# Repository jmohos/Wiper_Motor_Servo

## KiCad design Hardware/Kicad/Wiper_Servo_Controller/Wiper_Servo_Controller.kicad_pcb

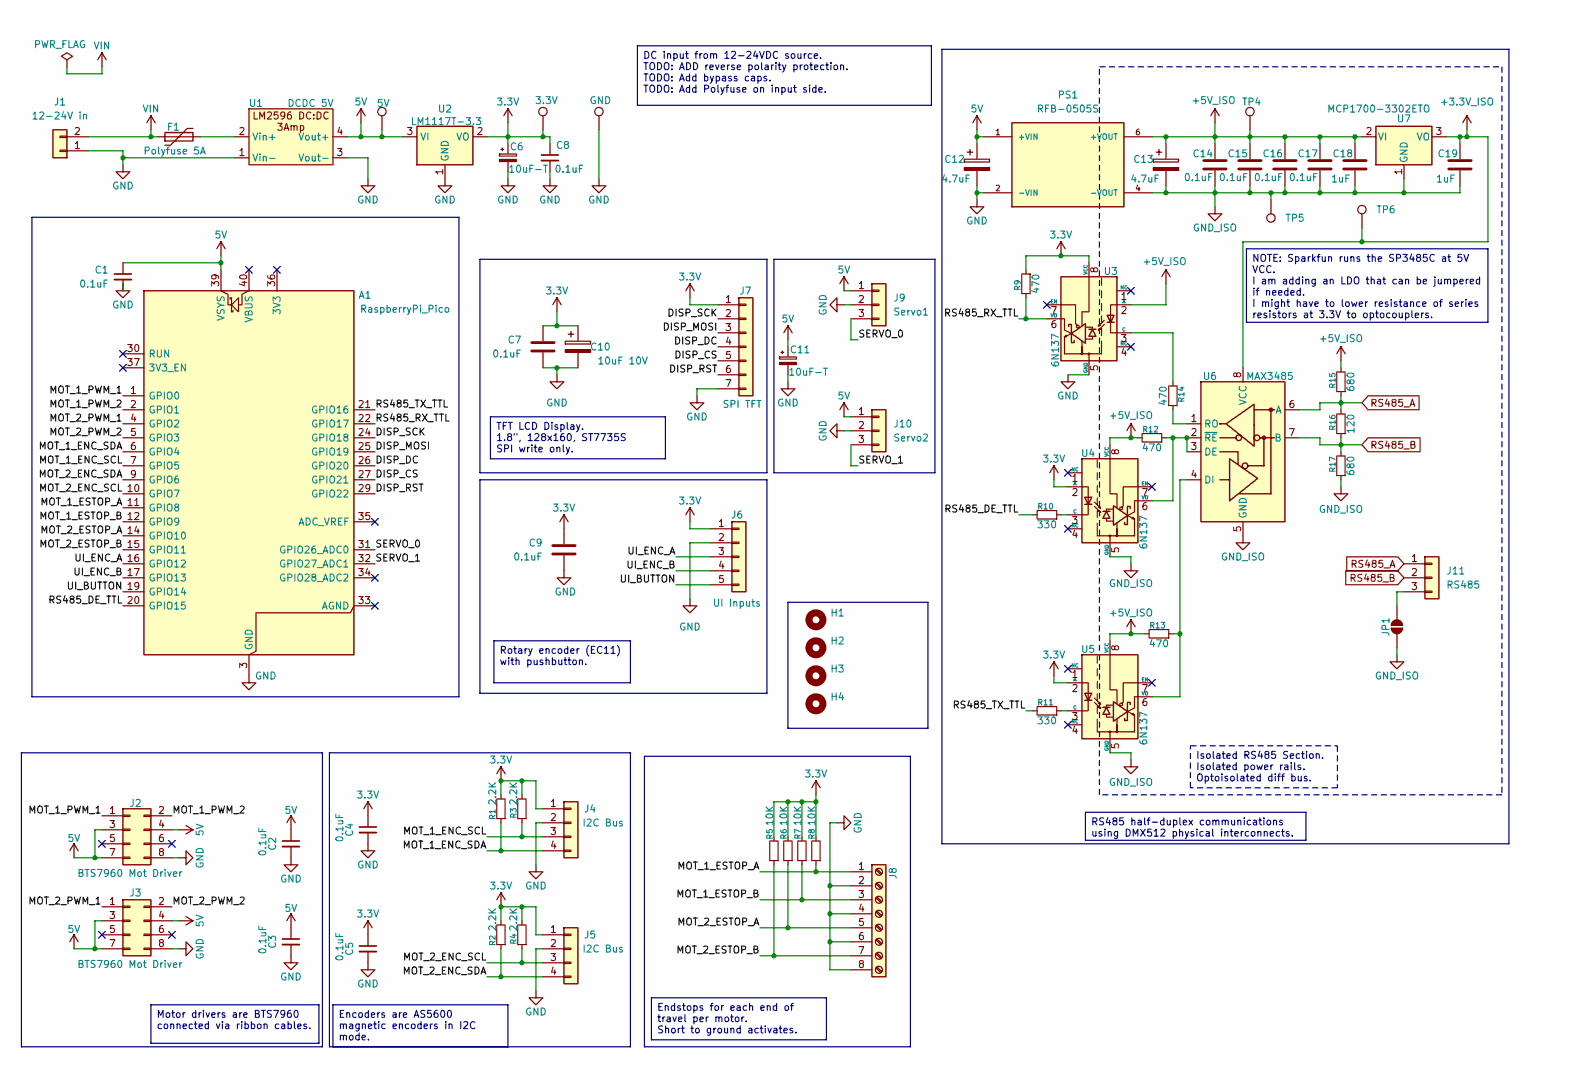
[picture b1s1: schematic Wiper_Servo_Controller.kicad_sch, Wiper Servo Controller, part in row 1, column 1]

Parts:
A1: RaspberryPi_Pico; RaspberryPi_Pico_Common_THT
C1, C2, C3, C4, C5, C7, C8, C9, C14, C15, C16, C17: 0.1uF; C_Disc_D5.1mm_W3.2mm_P5.00mm
C6, C11: 10uF-T; CP_Radial_Tantal_D5.5mm_P2.50mm
C10: 10uF 10V; CP_Radial_D5.0mm_P2.00mm
C12, C13: 4.7uF; CP_Radial_D5.0mm_P2.00mm
C18, C19: 1uF; C_Disc_D5.1mm_W3.2mm_P5.00mm
F1: Polyfuse 5A; Fuse_Littelfuse_395Series
H1, H2, H3, H4: MountingHole; MountingHole_3.2mm_M3
J1: 12-24V in; SolderWire-2sqmm_1x02_P7.8mm_D2mm_OD3.9mm
J2, J3: Conn_02x04_Odd_Even; IDC-Header_2x04_P2.54mm_Vertical
J4: Mot 1 Enc; JST_PH_B4B-PH-K_1x04_P2.00mm_Vertical
J5: Mot 2 Enc; JST_PH_B4B-PH-K_1x04_P2.00mm_Vertical
J6: UI Inputs; JST_PH_B5B-PH-K_1x05_P2.00mm_Vertical
J7: SPI TFT; JST_PH_B7B-PH-K_1x07_P2.00mm_Vertical
J8: Screw_Terminal_01x08; TerminalBlock_Phoenix_MPT-0,5-8-2.54_1x08_P2.54mm_Horizontal
J9: Servo1; JST_PH_B3B-PH-K_1x03_P2.00mm_Vertical
J10: Servo2; JST_PH_B3B-PH-K_1x03_P2.00mm_Vertical
J11: RS485; JST_PH_B3B-PH-K_1x03_P2.00mm_Vertical
JP1: Shield; SolderJumper-2_P1.3mm_Open_Pad1.0x1.5mm
PS1: RFB-0505S; CONV_RFB-0505S; PARTREV 1
R1, R2, R3, R4: 2.2K; R_Axial_DIN0207_L6.3mm_D2.5mm_P7.62mm_Horizontal
R5, R6, R7, R8: 10K; R_Axial_DIN0207_L6.3mm_D2.5mm_P7.62mm_Horizontal
R9, R12, R13, R14: 470; R_Axial_DIN0207_L6.3mm_D2.5mm_P7.62mm_Horizontal
R10, R11: 330; R_Axial_DIN0207_L6.3mm_D2.5mm_P7.62mm_Horizontal
R15, R17: 680; R_Axial_DIN0207_L6.3mm_D2.5mm_P7.62mm_Horizontal
R16: 120; R_Axial_DIN0207_L6.3mm_D2.5mm_P7.62mm_Horizontal
TP1: 5V; TestPoint_THTPad_D1.5mm_Drill0.7mm
TP2: 3.3V; TestPoint_THTPad_D1.5mm_Drill0.7mm
TP3: GND; TestPoint_THTPad_D1.5mm_Drill0.7mm
TP4: DMX_RX; TestPoint_THTPad_D1.5mm_Drill0.7mm
TP5: DMX_TX; TestPoint_THTPad_D1.5mm_Drill0.7mm
TP6: TestPoint_THTPad_D1.5mm_Drill0.7mm
U1: DCDC 5V; DCDC_Converter_LM2596_3A
U2: LM1117T-3.3; TO-220-3_Vertical
U3, U4, U5: 6N137; SMDIP-8_W9.53mm
U6: MAX3485; SOIC-8_3.9x4.9mm_P1.27mm
U7: MCP1700-3302ETO; TO-92_Inline

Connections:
3.3V: C4.1, C5.1, C6.1, C7.1, C8.1, C9.1, C10.1, J4.1, J5.1, J6.1, J7.1, R1.2, R2.2, R3.2, R4.2, R5.2, R6.2, R7.2, R8.2, R9.1, TP2.1, U2.2 (VO), U3.8 (VCC), U4.2 (A), U5.2 (A)
5V: A1.39 (VSYS), C1.1, C2.1, C3.1, C11.1, C12.1, J2.3, J2.4, J2.7, J3.3, J3.4, J3.7, J9.1, J10.1, PS1.1 (+VIN), TP1.1, U1.4 (Vout+), U2.3 (VI)
+3.3V_ISO: C19.1, TP6.1, U6.8 (VCC), U7.3 (VO)
+5V_ISO: C13.1, C14.1, C15.1, C16.1, C17.1, C18.1, PS1.6 (+VOUT), R12.2, R13.2, R15.2, TP4.1, U3.2 (A), U4.8 (VCC), U5.8 (VCC), U7.2 (VI)
/DISP_CS: A1.27 (GPIO21), J7.5
/DISP_DC: A1.26 (GPIO20), J7.4
/DISP_MOSI: A1.25 (GPIO19), J7.3
/DISP_RST: A1.29 (GPIO22), J7.6
/DISP_SCK: A1.24 (GPIO18), J7.2
/MOT_1_ENC_SCL: A1.7 (GPIO5), J4.3, R3.1
/MOT_1_ENC_SDA: A1.6 (GPIO4), J4.4, R1.1
/MOT_1_ESTOP_A: A1.11 (GPIO8), J8.1, R8.1
/MOT_1_ESTOP_B: A1.12 (GPIO9), J8.3, R7.1
/MOT_1_PWM_1: A1.1 (GPIO0), J2.1
/MOT_1_PWM_2: A1.2 (GPIO1), J2.2
/MOT_2_ENC_SCL: A1.10 (GPIO7), J5.3, R4.1
/MOT_2_ENC_SDA: A1.9 (GPIO6), J5.4, R2.1
/MOT_2_ESTOP_A: A1.14 (GPIO10), J8.5, R6.1
/MOT_2_ESTOP_B: A1.15 (GPIO11), J8.7, R5.1
/MOT_2_PWM_1: A1.4 (GPIO2), J3.1
/MOT_2_PWM_2: A1.5 (GPIO3), J3.2
/RS485_DE_TTL: A1.20 (GPIO15), R10.2
/RS485_RX_TTL: A1.22 (GPIO17), R9.2, U3.6 (VO)
/RS485_TX_TTL: A1.21 (GPIO16), R11.2
/SERVO_0: A1.31 (GPIO26_ADC0), J9.3
/SERVO_1: A1.32 (GPIO27_ADC1), J10.3
/UI_BUTTON: A1.19 (GPIO14), J6.5
/UI_ENC_A: A1.16 (GPIO12), J6.3
/UI_ENC_B: A1.17 (GPIO13), J6.4
GND: A1.3 (GND), A1.8 (GND), A1.13 (GND), A1.18 (GND), A1.23 (GND), A1.28 (GND), A1.38 (GND), C1.2, C2.2, C3.2, C4.2, C5.2, C6.2, C7.2, C8.2, C9.2, C10.2, C11.2, C12.2, J1.1, J2.8, J3.8, J4.2, J5.2, J6.2, J7.7, J8.2, J8.4, J8.6, J8.8, J9.2, J10.2, PS1.2 (-VIN), TP3.1, U1.1 (Vin-), U1.3 (Vout-), U2.1 (GND), U3.5 (GND)
GND_ISO: C13.2, C14.2, C15.2, C16.2, C17.2, C18.2, C19.2, JP1.1 (A), PS1.4 (-VOUT), R17.1, TP5.1, U4.5 (GND), U5.5 (GND), U6.5 (GND), U7.1 (GND)
unnamed: J11.3, JP1.2 (B)
unnamed: F1.2, U1.2 (Vin+)
unnamed: R14.2, U3.3 (C)
unnamed: R10.1, U4.3 (C)
unnamed: R12.1, U4.6 (VO), U6.2 (~RE), U6.3 (DE)
unnamed: R11.1, U5.3 (C)
unnamed: R13.1, U5.6 (VO), U6.4 (DI)
unnamed: R14.1, U6.1 (RO)
RS485_A: J11.1, R15.1, R16.2, U6.6 (A)
RS485_B: J11.2, R16.1, R17.2, U6.7 (B)
VIN: F1.1, J1.2

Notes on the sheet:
RS485 half-duplex communications using DMX512 physical interconnects.
Motor drivers are BTS7960 connected via ribbon cables.
TFT LCD Display. 1.8", 128x160, ST7735S SPI write only.
Isolated RS485 Section. Isolated power rails. Optoisolated diff bus.
DC input from 12-24VDC source. TODO: ADD reverse polarity protection. TODO: Add bypass caps. TODO: Add Polyfuse on input side.
NOTE: Sparkfun runs the SP3485C at 5V VCC. I am adding an LDO that can be jumpered if needed. I might have to lower resistance of series resistors at 3.3V to optocouplers.
Rotary encoder (EC11) with pushbutton.
Endstops for each end of travel per motor. Short to ground activates.
Encoders are AS5600 magnetic encoders in I2C mode.

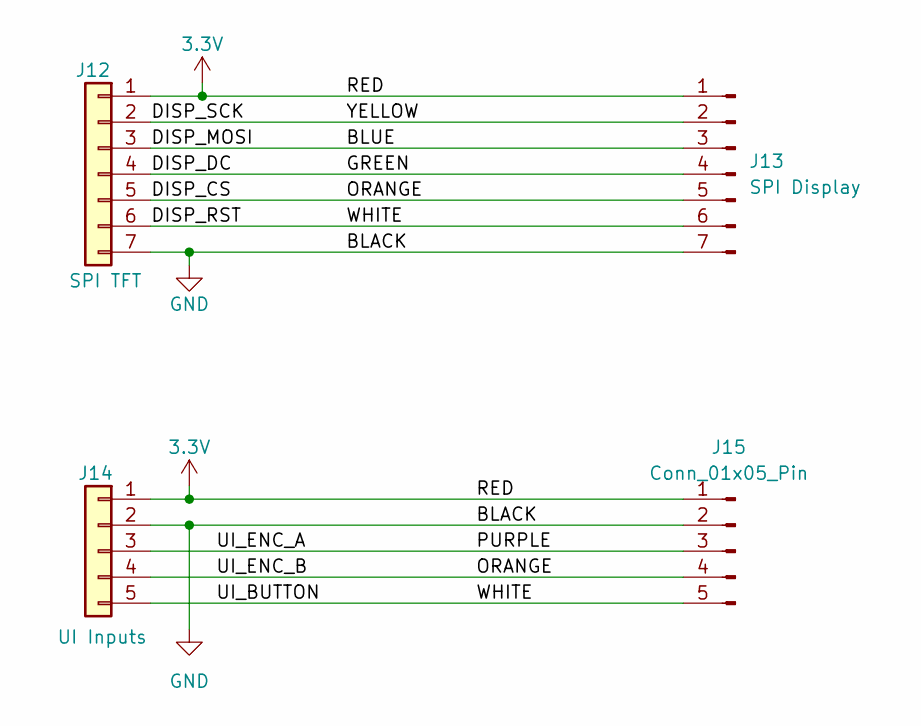
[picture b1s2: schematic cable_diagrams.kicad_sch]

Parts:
J12: SPI TFT; JST_PH_B7B-PH-K_1x07_P2.00mm_Vertical
J13: SPI Display
J14: UI Inputs; JST_PH_B5B-PH-K_1x05_P2.00mm_Vertical
J15: Conn_01x05_Pin

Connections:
unnamed: J12.1, J13.1, J14.1, J15.1
unnamed: J12.2, J13.2
unnamed: J12.3, J13.3
unnamed: J12.4, J13.4
unnamed: J12.5, J13.5, J14.4, J15.4
unnamed: J12.6, J13.6, J14.5, J15.5
unnamed: J12.7, J13.7, J14.2, J15.2
unnamed: J14.3, J15.3

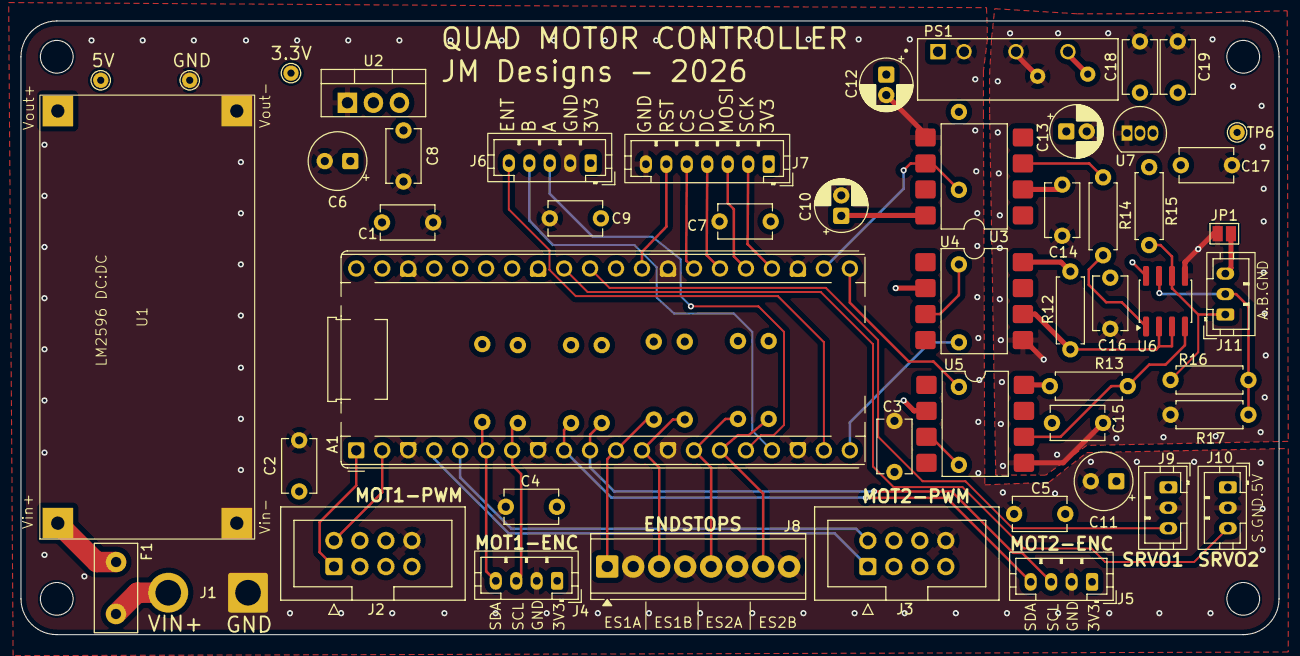
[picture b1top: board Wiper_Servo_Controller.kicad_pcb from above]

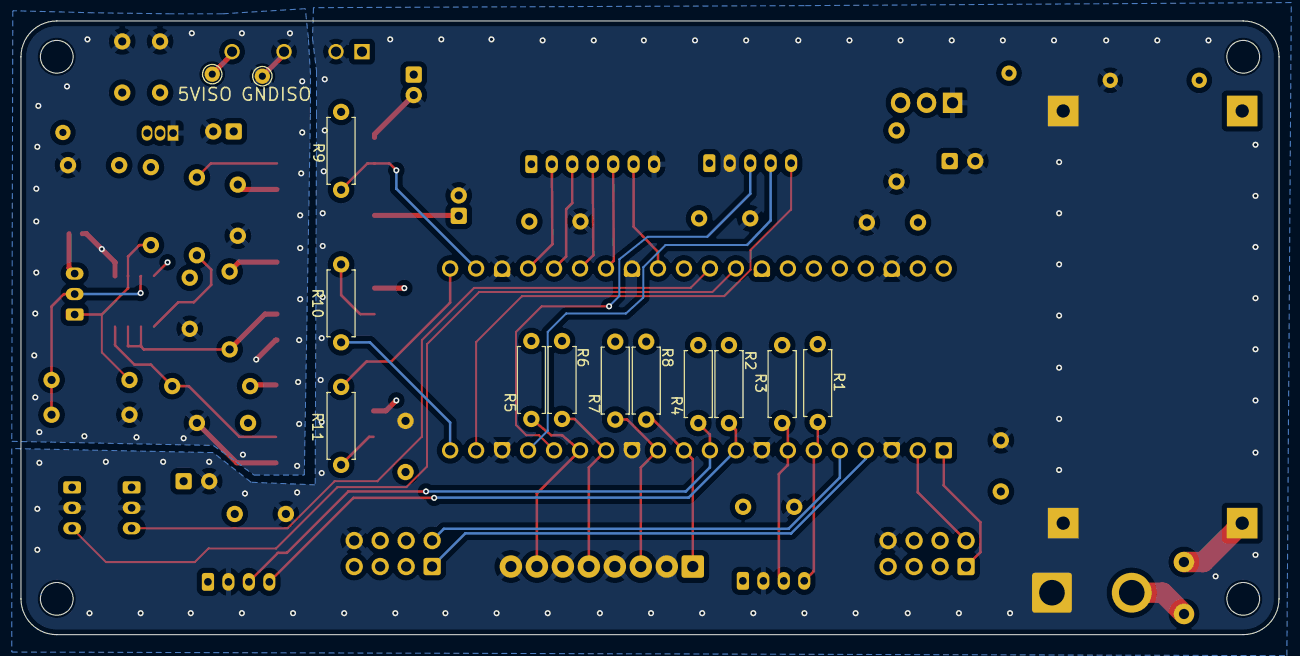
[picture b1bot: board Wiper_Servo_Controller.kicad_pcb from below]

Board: 6 copper layers, 123.0 x 60.0 mm, 68 parts (13 on the bottom side), 42 nets.

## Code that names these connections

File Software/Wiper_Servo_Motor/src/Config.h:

#pragma once
// =============================================================================
//  Config.h — RP2040 Dual Brushless Wiper Motor Controller
//
//  Hardware:
//    Motor drivers : BTS7960 ×2
//      Motor 0: IN1=GPIO0 (PWM slice 0A), IN2=GPIO1 (PWM slice 0B)
//      Motor 1: IN1=GPIO2 (PWM slice 1A), IN2=GPIO3 (PWM slice 1B)
//    Encoders      : AS5600 magnetic angle sensor ×2, separate I2C buses
//      Motor 0: I2C0 SDA=GPIO4, SCL=GPIO5
//      Motor 1: I2C1 SDA=GPIO6, SCL=GPIO7
//    Endstops      : 2 per motor, active-low, internal pull-up
//      Motor 0: End-A=GPIO8,  End-B=GPIO9
//      Motor 1: End-A=GPIO10, End-B=GPIO11
//    AnimCom RS485 : UART0, RS485 transceiver
//      DE=GPIO15, TX=GPIO16, RX=GPIO17
//    Local UI      : Rotary encoder + button
//      ENC_CLK=GPIO12, ENC_DT=GPIO13, ENC_SW=GPIO14
//    Local UI      : SPI OLED display (SPI0)
//      SCK=GPIO18, MOSI=GPIO19, DC=GPIO20, CS=GPIO21, RST=GPIO22
//    Status LED    : GPIO25 (LED_BUILTIN)
//    RC Servos     : Servo 0=GPIO26, Servo 1=GPIO27 (PWM slice 5, Servo lib)
// =============================================================================
#include <Arduino.h>

// ---------------------------------------------------------------------------
// Motor driver pin assignments — BTS7960 ×2
//   Each motor has an IN1 (forward PWM) and IN2 (reverse PWM) pin.
//   Both pins of a motor must be on the same RP2040 PWM slice so that
//   the complementary outputs share a common counter.
//   Motor 0: slice 0  (GPIO0 / GPIO1)
//   Motor 1: slice 1  (GPIO2 / GPIO3)
// ---------------------------------------------------------------------------
#define MOTOR_0_IN1_PIN   1   // PWM slice 0A — forward
#define MOTOR_0_IN2_PIN   0   // PWM slice 0B — reverse
#define MOTOR_1_IN1_PIN   3   // PWM slice 1A — forward
#define MOTOR_1_IN2_PIN   2   // PWM slice 1B — reverse
#define NUM_MOTORS        2

// ---------------------------------------------------------------------------
// PWM parameters — 25 kHz, 5000-step duty range
//
// analogWriteFreq() / analogWriteRange() are global, so both slices run at
// exactly the same 25 kHz base — no inter-motor frequency drift.
// ---------------------------------------------------------------------------
#define PWM_FREQ_HZ   25000
#define PWM_WRAP      4999    // duty range: 0 … PWM_WRAP (inclusive)

// ---------------------------------------------------------------------------
// I2C0 — Motor 0 AS5600 encoder (Pico as MASTER)
// ---------------------------------------------------------------------------
#define AS5600_0_SDA_PIN    4
#define AS5600_0_SCL_PIN    5
#define AS5600_I2C_FREQ     400000   // 400 kHz fast-mode (applied to both buses)

// ---------------------------------------------------------------------------
// I2C1 — Motor 1 AS5600 encoder (Pico as MASTER)
//   NOTE: Wire1 is reserved as I2C MASTER for this encoder.
//         The former I2C slave interface (GPIO26/27) has been retired;
//         local control is now provided by the OLED + rotary encoder.
// ---------------------------------------------------------------------------
#define AS5600_1_SDA_PIN    6
#define AS5600_1_SCL_PIN    7

// ---------------------------------------------------------------------------
// Endstop switches — active-low, configured INPUT_PULLUP
// ---------------------------------------------------------------------------
#define ENDSTOP_M0_A_PIN    8
#define ENDSTOP_M0_B_PIN    9
#define ENDSTOP_M1_A_PIN   10
#define ENDSTOP_M1_B_PIN   11

// ---------------------------------------------------------------------------
// AnimCom RS485 serial interface (UART0, RS485 transceiver)
//   DE  = GPIO15  Direction enable: driven LOW (receive only, unidirectional)
//   TX  = GPIO16  UART0 TX — not actively used (protocol is receive-only)
//   RX  = GPIO17  UART0 RX — AnimCom frames from Animation Controller
//
//   Baud rate: 115200, 8N1 (AnimCom standard)
//   Use Serial1 (UART0) in the arduino-pico core.
// ---------------------------------------------------------------------------
#define RS485_DE_PIN  15   // RS485 direction enable (driven LOW = receive)
#define RS485_TX_PIN  16   // UART0 TX (declared but unused)
#define RS485_RX_PIN  17   // UART0 RX
#define RS485_BAUD   115200

// Node identity — change to a unique station ID (0x03-0x09) for each unit.
#define NODE_ID      0x03

// ---------------------------------------------------------------------------
// Local UI — rotary encoder with pushbutton
// ---------------------------------------------------------------------------
#define ENC_CLK_PIN   12   // Encoder channel A
#define ENC_DT_PIN    13   // Encoder channel B
#define ENC_SW_PIN    14   // Pushbutton (active-low)

// ---------------------------------------------------------------------------
// Local UI — SPI OLED display (SPI0)
// ---------------------------------------------------------------------------
#define DISP_SCK_PIN    18   // SPI0 SCK
#define DISP_MOSI_PIN   19   // SPI0 TX / MOSI
#define DISP_DC_PIN     20   // Data / Command select
#define DISP_CS_PIN     21   // Chip select (active-low)
#define DISP_RST_PIN    22   // Reset (active-low; tie HIGH if unused)

// SPI clock for the display.  Lower this if the display is unresponsive or
// shows corruption — long/unshielded wires may require 1–4 MHz.
#define DISP_SPI_FREQ   8000000UL   // 8 MHz

// ---------------------------------------------------------------------------
// Safety watchdog
// If no valid command is received within this window the motors are coasted.
// ---------------------------------------------------------------------------
#define WATCHDOG_TIMEOUT_MS  5000

// ---------------------------------------------------------------------------
// Status LED
// ---------------------------------------------------------------------------
#define STATUS_LED_PIN  LED_BUILTIN

// ---------------------------------------------------------------------------
// RC Servo outputs — standard 50 Hz PWM (1–2 ms pulse width, 0–180°)
//   Servo 0: GPIO26  (PWM slice 5A)
//   Servo 1: GPIO27  (PWM slice 5B)
//
//   IMPORTANT: Use the arduino-pico Servo library, NOT analogWrite(), to
//   avoid reconfiguring the global motor PWM frequency (analogWriteFreq()
//   affects all slices; Servo library configures hardware registers directly).
// ---------------------------------------------------------------------------
#define SERVO_0_PIN  26
#define SERVO_1_PIN  27
#define NUM_SERVOS   2

// ---------------------------------------------------------------------------
// Legacy — I2C slave (GPIO26/27) retired.  Symbols kept only to avoid
// breaking I2CSlave.cpp compilation.  I2CSlave::begin() must NOT be called.
// ---------------------------------------------------------------------------
#define I2C_SDA_PIN  26   // deprecated — do not use
#define I2C_SCL_PIN  27   // deprecated — do not use

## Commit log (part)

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2026-03-24 Adding servo ramping and LCD display output.
2026-03-24 Added servo outputs.
2026-03-24 Eliminating backup folder from repo.
2026-03-24 Eliminating backup zips from repo.
2026-04-01 Switch from DMX to RS485
2026-04-06 Updated to new screen.
2026-04-07 Fixed compatibility with the animation controller man mode.
2026-04-10 Change to animation mode default. Menu cleanup.
2026-04-12 Enhanced console with stream on/off. Added bootload support to prevent needing to use BOOT button. Added meter animation with wiggle.
2026-04-15 Basic robot animation done.
